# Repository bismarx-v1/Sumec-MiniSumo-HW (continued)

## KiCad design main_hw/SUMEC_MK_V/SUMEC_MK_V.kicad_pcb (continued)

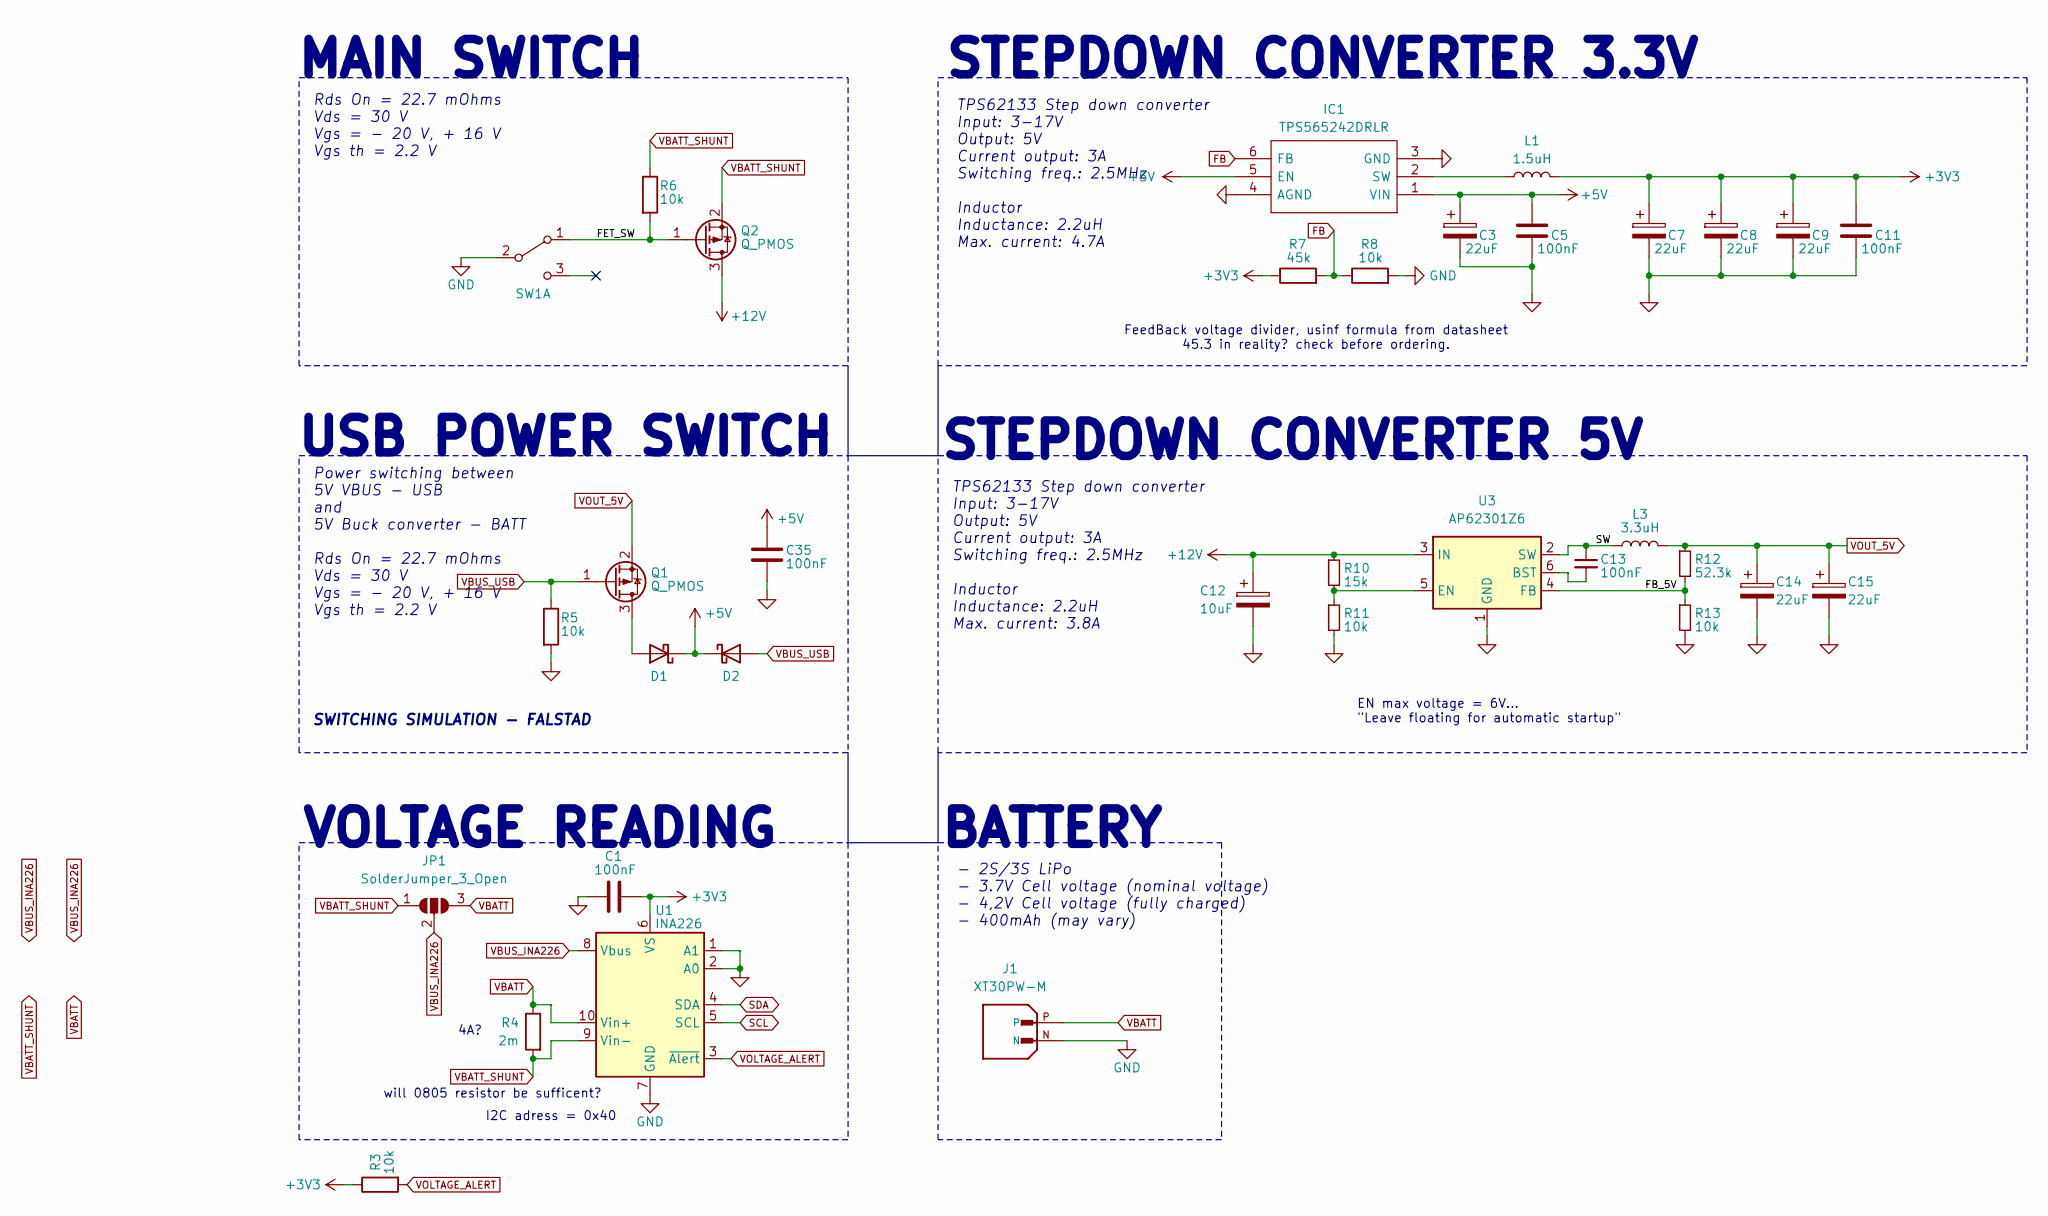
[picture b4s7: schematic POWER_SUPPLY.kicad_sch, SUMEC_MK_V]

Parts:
C1, C13, C35: 100nF; C_0805_2012Metric_Pad1.18x1.45mm_HandSolder
C3, C7, C8, C9, C14, C15: 22uF; CP_EIA-2012-12_Kemet-R_Pad1.30x1.05mm_HandSolder
C5, C11: 100nF; C_0805_2012Metric_Pad1.18x1.45mm_HandSolder; LCSC C49678
C12: 10uF; CP_EIA-3216-18_Kemet-A_Pad1.58x1.35mm_HandSolder
D1, D2: D_Schottky; D_1206_3216Metric_Pad1.42x1.75mm_HandSolder
IC1: TPS565242DRLR; SOT-563; Manufacturer_Part_Number TPS565242DRLR; Mouser Part Number 595-TPS565242DRLR
J1: XT30PW-M; PARTREV 1.2
JP1: SolderJumper_3_Open; SolderJumper-3_P2.0mm_Open_TrianglePad1.0x1.5mm
L1: 1.5uH; L_Vishay_IHLP-1212
L3: 3.3uH; L_Vishay_IHLP-1616
Q1, Q2: Q_PMOS; SOT-23-3
R3, R5, R6, R11, R13: 10k; R_0805_2012Metric_Pad1.20x1.40mm_HandSolder
R4: 2m; R_0805_2012Metric_Pad1.20x1.40mm_HandSolder
R7: 45k; R_0805_2012Metric_Pad1.20x1.40mm_HandSolder; LCSC C17470
R8: 10k; R_0805_2012Metric_Pad1.20x1.40mm_HandSolder; LCSC C17633
R10: 15k; R_0805_2012Metric_Pad1.20x1.40mm_HandSolder
R12: 52.3k; R_0805_2012Metric_Pad1.20x1.40mm_HandSolder
SW1: SW_DPDT_x2; Custom_SPDT_2.5_Switch
U1: INA226; VSSOP-10_3x3mm_P0.5mm
U3: AP62301Z6; SOT-563

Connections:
+3V3: C1.2, C7.1, C8.1, C9.1, C11.1, L1.2, R3.1, R7.1, U1.6 (VS); also elsewhere on the board
+5V: C3.1, C5.1, C35.1, D1.1 (K), D2.1 (K), IC1.1 (VIN), IC1.5 (EN); also elsewhere on the board
+12V: C12.1, Q2.3 (D), R10.1, U3.3 (IN); also elsewhere on the board
/POWER/FB_5V: R12.2, R13.1, U3.4 (FB)
/POWER/FET_SW: Q2.1 (G), R6.2, SW1.1 (A)
/POWER/SW: C13.1, L3.1, U3.2 (SW)
FB: IC1.6 (FB), R7.2, R8.1
GND: C1.1, C3.2, C5.2, C7.2, C8.2, C9.2, C11.2, C12.2, C14.2, C15.2, C35.2, IC1.3 (GND), IC1.4 (AGND), J1.N, R5.2, R8.2, R11.2, R13.2, SW1.2 (B), U1.1 (A1), U1.2 (A0), U1.7 (GND), U3.1 (GND); also elsewhere on the board
unnamed: D1.2 (A), Q1.3 (D)
unnamed: IC1.2 (SW), L1.1
unnamed: C13.2, U3.6 (BST)
unnamed: R10.2, R11.1, U3.5 (EN)
SCL: U1.5 (SCL); also elsewhere on the board
SDA: U1.4 (SDA); also elsewhere on the board
VBATT: J1.P, JP1.3 (B), R4.1, U1.10 (Vin+)
VBATT_SHUNT: JP1.1 (A), Q2.2 (S), R4.2, R6.1, U1.9 (Vin-)
VBUS_INA226: JP1.2 (C), U1.8 (Vbus)
VBUS_USB: D2.2 (A), Q1.1 (G), R5.1; also elsewhere on the board
VOLTAGE_ALERT: R3.2, U1.3 (~Alert); also elsewhere on the board
VOUT_5V: C14.1, C15.1, L3.2, Q1.2 (S), R12.1

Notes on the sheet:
SWITCHING SIMULATION - FALSTAD
TPS62133 Step down converter Input: 3-17V Output: 5V Current output: 3A Switching freq.: 2.5MHz Inductor Inductance: 2.2uH Max. current: 4.7A
BATTERY
USB POWER SWITCH
Power switching between 5V VBUS - USB and 5V Buck converter - BATT
MAIN SWITCH
I2C adress = 0x40
STEPDOWN CONVERTER 3.3V
STEPDOWN CONVERTER 5V
VOLTAGE READING
Rds On = 22.7 mOhms Vds = 30 V Vgs = - 20 V, + 16 V Vgs th = 2.2 V
- 2S/3S LiPo - 3.7V Cell voltage (nominal voltage) - 4,2V Cell voltage (fully charged) - 400mAh (may vary)
TPS62133 Step down converter Input: 3-17V Output: 5V Current output: 3A Switching freq.: 2.5MHz Inductor Inductance: 2.2uH Max. current: 3.8A
4A?
FeedBack voltage divider, usinf formula from datasheet 45.3 in reality? check before ordering.
will 0805 resistor be sufficent?
EN max voltage = 6V... "Leave floating for automatic startup"

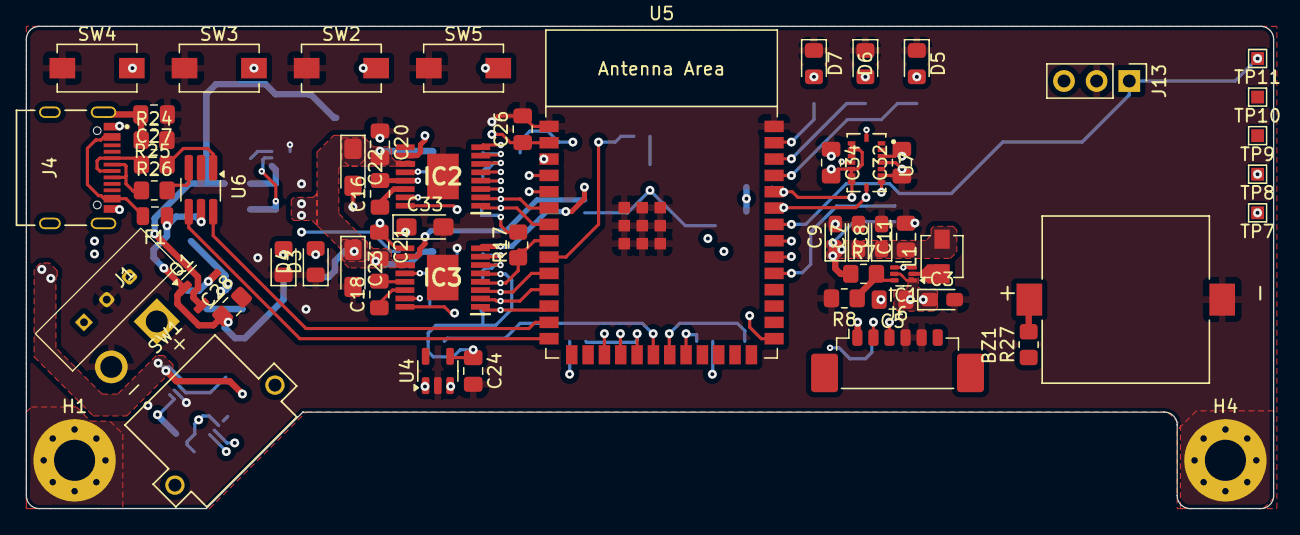
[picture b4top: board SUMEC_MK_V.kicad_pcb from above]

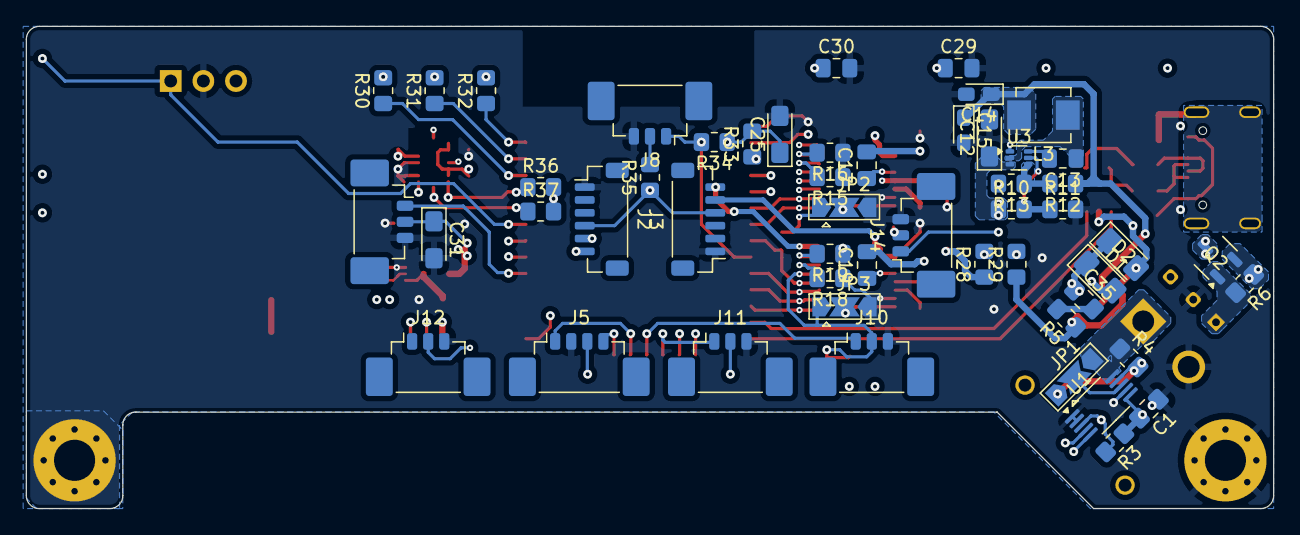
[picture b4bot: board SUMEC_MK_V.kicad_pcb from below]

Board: 4 copper layers, 97.0 x 37.5 mm, 110 parts (52 on the bottom side), 74 nets.

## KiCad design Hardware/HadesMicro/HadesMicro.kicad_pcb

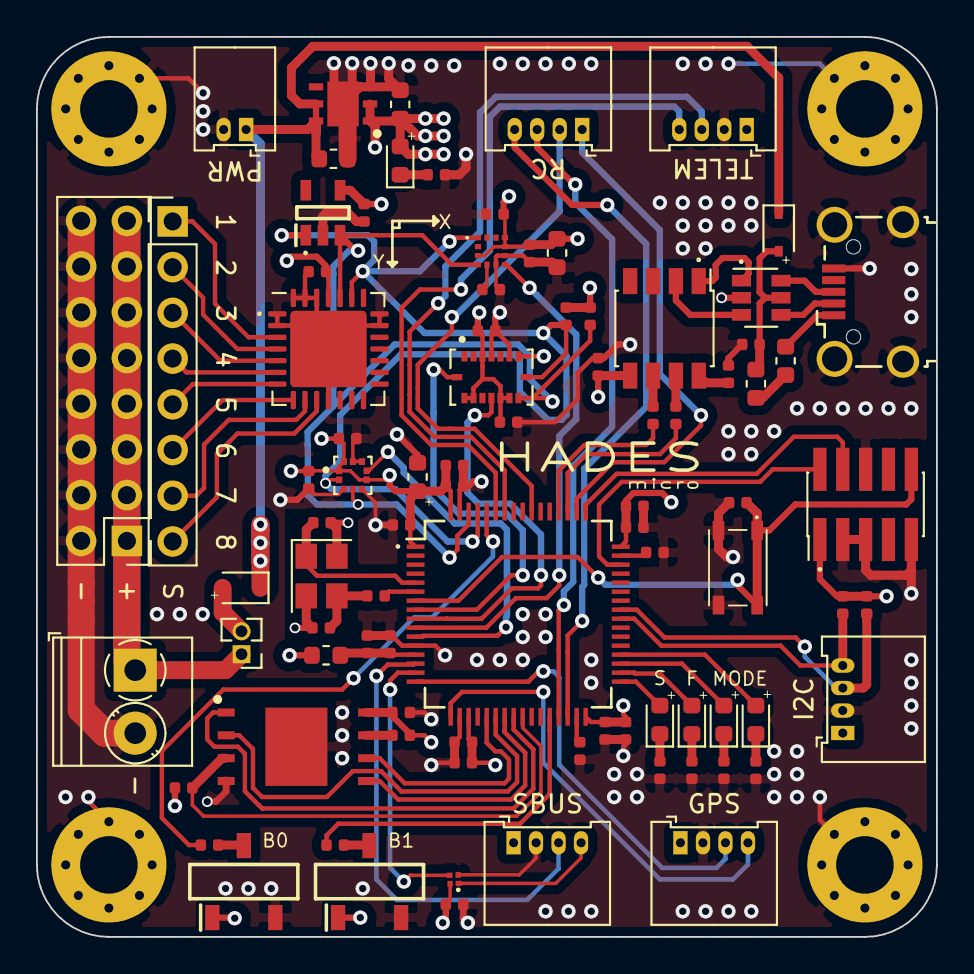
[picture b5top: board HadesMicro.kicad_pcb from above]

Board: 4 copper layers, 50.0 x 50.0 mm, 6 parts (0 on the bottom side), 2 nets.

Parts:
GPS: Conn_01x04; Molex_PicoBlade_53048-0810_1x04_P1.25mm_Horizontal
I2C: Conn_01x04; Molex_PicoBlade_53048-0810_1x04_P1.25mm_Horizontal
PWR: Conn_01x02; Molex_PicoBlade_53048-0410_1x02_P1.25mm_Horizontal
SBUS: Conn_01x04; Molex_PicoBlade_53048-0810_1x04_P1.25mm_Horizontal
SWD: Conn_02x05_Counter_Clockwise; PinHeader_2x05_P1.27mm_Vertical_SMD
TELEM: Conn_01x04; Molex_PicoBlade_53048-0810_1x04_P1.25mm_Horizontal

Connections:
+3V3: GPS.1, I2C.1, SBUS.1, SWD.1, TELEM.1
GND: GPS.2, I2C.2, PWR.2, SBUS.2, SWD.3, SWD.5, SWD.6, SWD.9, TELEM.2

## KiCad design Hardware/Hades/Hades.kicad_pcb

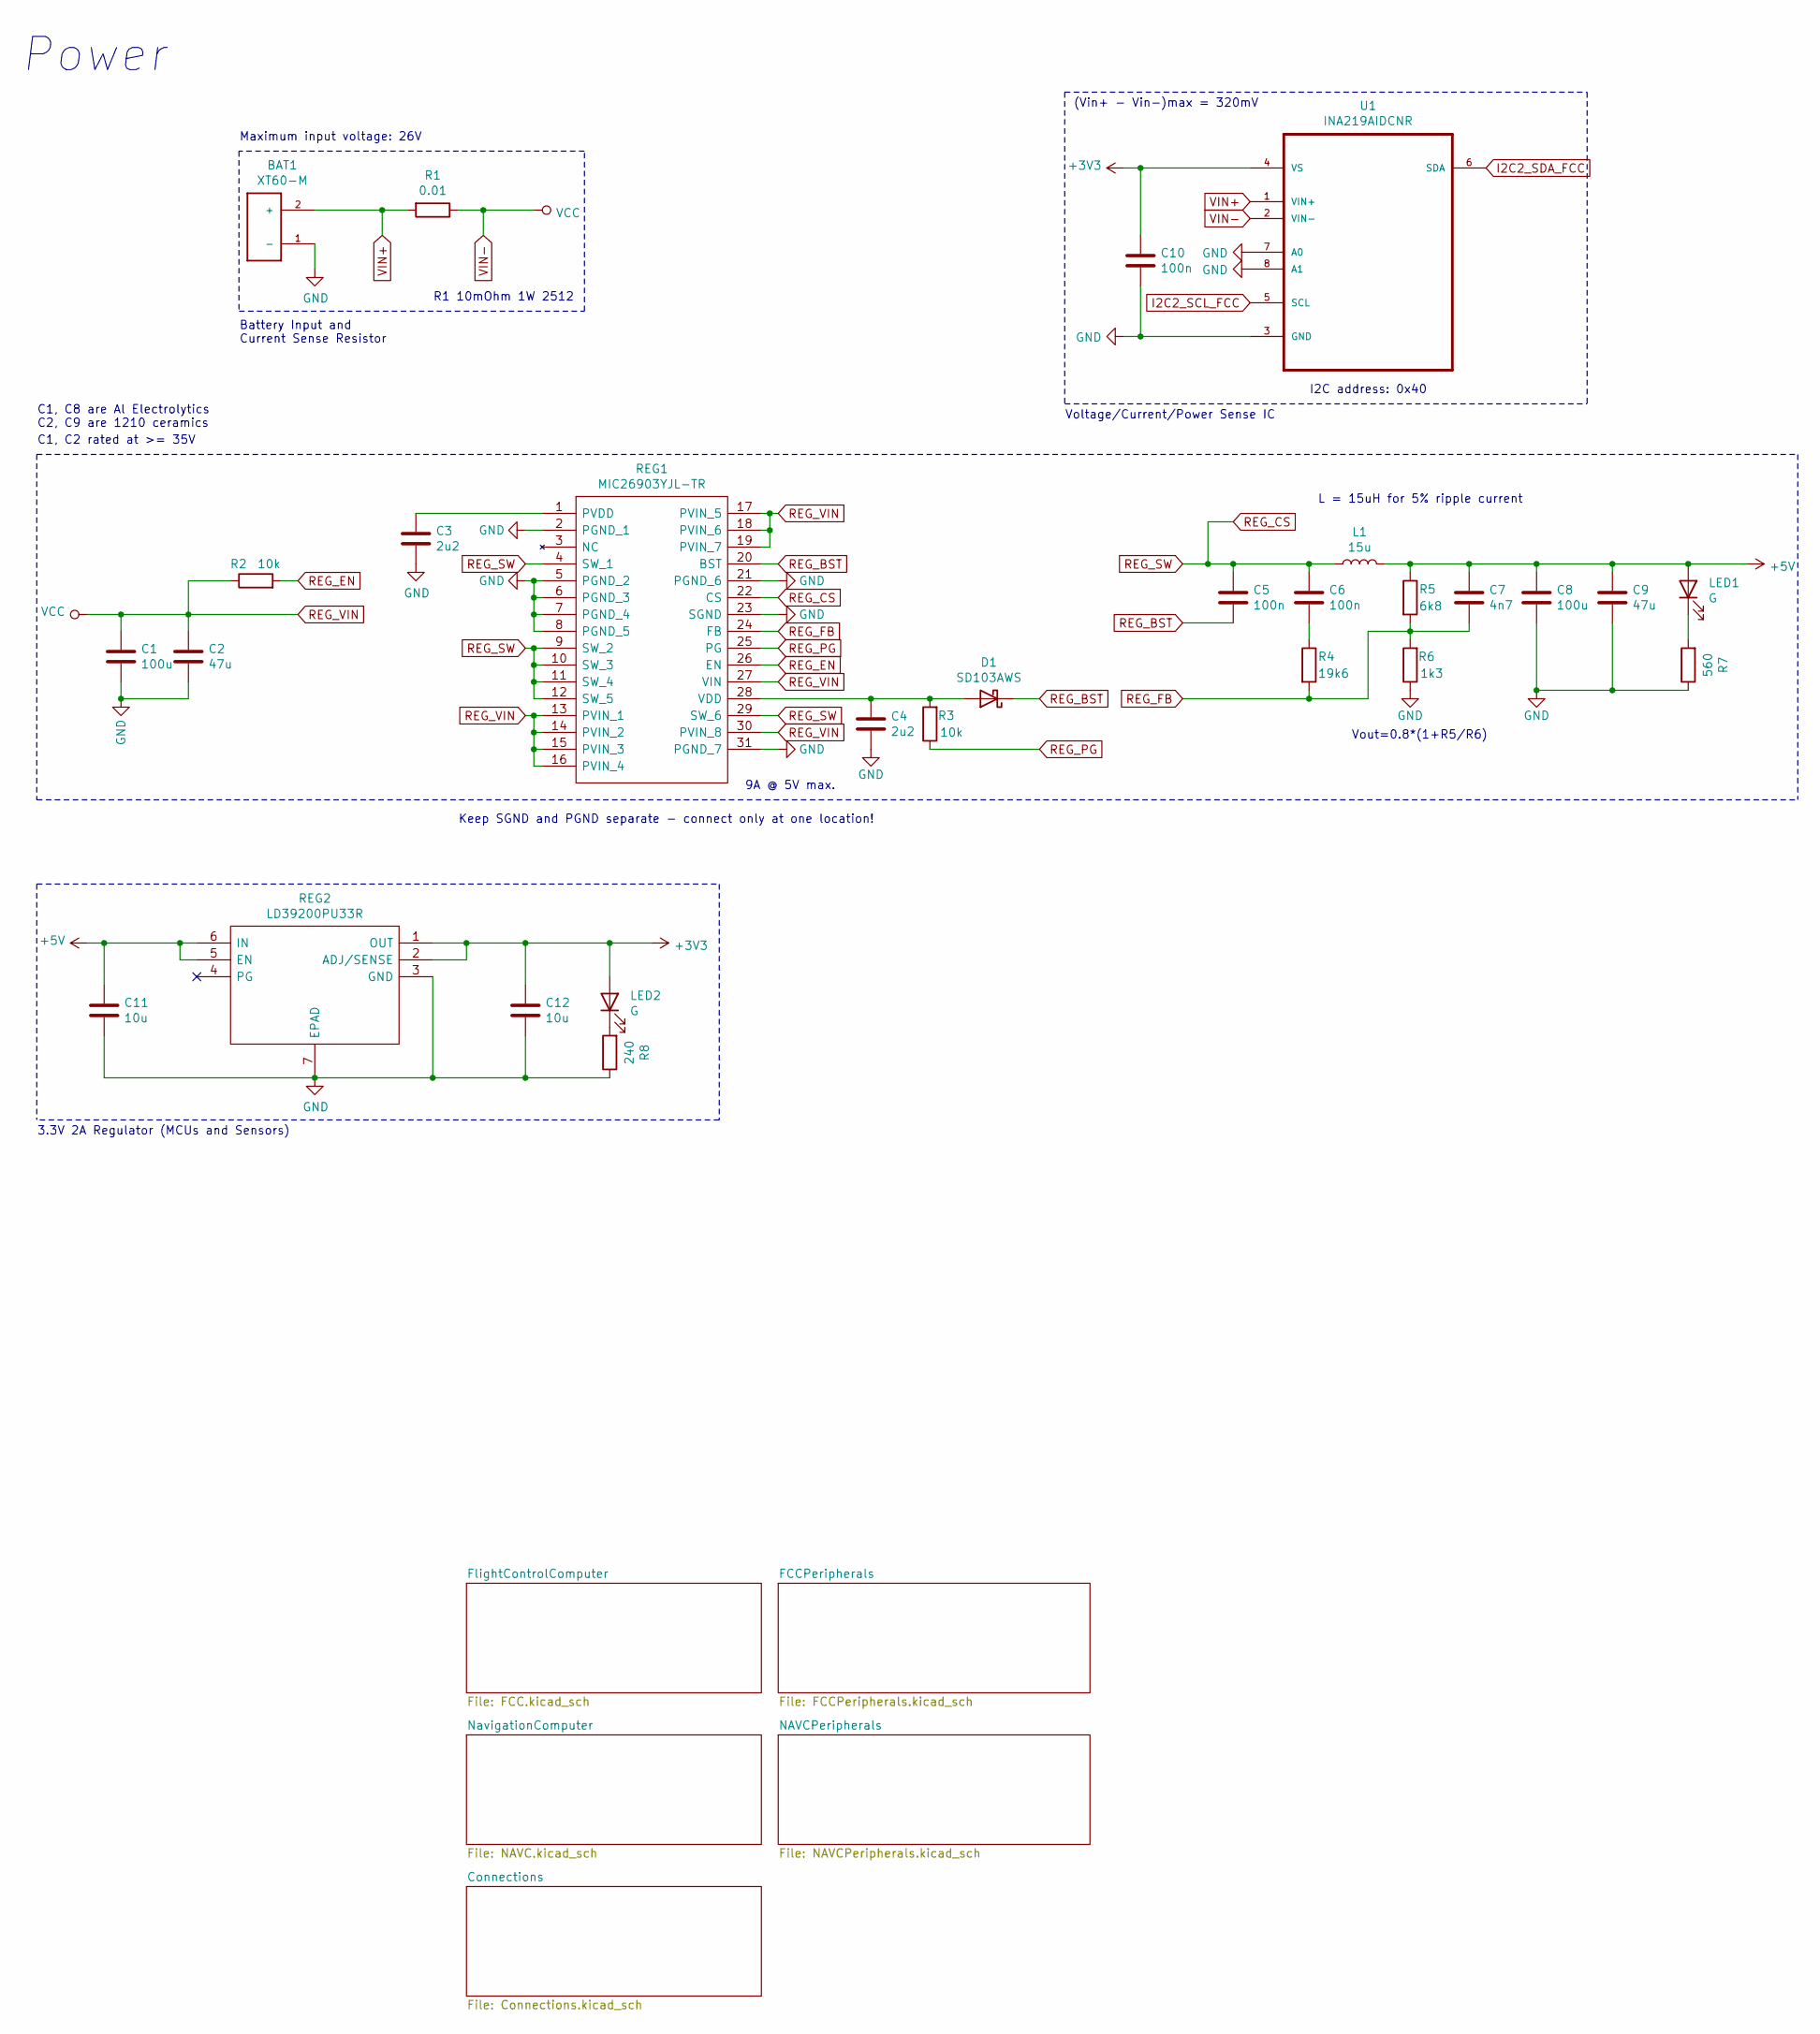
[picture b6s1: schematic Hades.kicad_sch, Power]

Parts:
BAT1: XT60-M; AMASS_XT60-M
C1, C8: 100u; C_Elec_6.3x7.7
C2, C9: 47u; C_1210_3225Metric
C3, C4: 2u2; C_0805_2012Metric
C5, C6: 100n; C_0805_2012Metric
C7: 4n7; C_0805_2012Metric
C10: 100n; C_0402_1005Metric
C11, C12: 10u; C_0603_1608Metric
D1: SD103AWS; D_SOD-323
L1: 15u; INDPM135125X650N
LED1, LED2: G; LED_0603_1608Metric
R1: 0.01; R_2512_6332Metric
R2, R3: 10k; R_0805_2012Metric
R4: 19k6; R_0805_2012Metric
R5: 6k8; R_0805_2012Metric
R6: 1k3; R_0805_2012Metric
R7: 560; R_0603_1608Metric
R8: 240; R_0603_1608Metric
REG1: MIC26903YJL-TR; MIC24054YJLTR; Manufacturer_Part_Number MIC26903YJL-TR; Mouser Part Number 998-MIC26903YJLTR
REG2: LD39200PU33R; SON95P300X300X100-7N-D; Manufacturer_Part_Number LD39200PU33R; Mouser Part Number 511-LD39200PU33R
U1: INA219AIDCNR; SOT65P280X145-8N

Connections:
+3V3: C10.1, C12.1, LED2.2 (A), REG2.1 (OUT), REG2.2 (ADJ/SENSE), U1.4 (VS); also elsewhere on the board
+5V: C7.1, C8.1, C9.1, C11.1, L1.2, LED1.2 (A), R5.1, REG2.5 (EN), REG2.6 (IN); also elsewhere on the board
GND: BAT1.1 (-), C1.2, C2.2, C3.2, C4.2, C8.2, C9.2, C10.2, C11.2, C12.2, R6.1, R7.1, R8.1, REG1.2 (PGND_1), REG1.5 (PGND_2), REG1.6 (PGND_3), REG1.7 (PGND_4), REG1.8 (PGND_5), REG1.21 (PGND_6), REG1.23 (SGND), REG1.31 (PGND_7), REG2.3 (GND), REG2.7 (EPAD), U1.3 (GND), U1.7 (A0), U1.8 (A1); also elsewhere on the board
I2C2_SCL_FCC: U1.5 (SCL); also elsewhere on the board
I2C2_SDA_FCC: U1.6 (SDA); also elsewhere on the board
unnamed: C3.1, REG1.1 (PVDD)
unnamed: C4.1, D1.2 (A), R3.2, REG1.28 (VDD)
unnamed: C6.2, R4.1
unnamed: LED1.1 (K), R7.2
unnamed: LED2.1 (K), R8.2
REG_BST: C5.2, D1.1 (K), REG1.20 (BST)
REG_CS: C5.1, C6.1, L1.1, REG1.4 (SW_1), REG1.9 (SW_2), REG1.10 (SW_3), REG1.11 (SW_4), REG1.12 (SW_5), REG1.22 (CS), REG1.29 (SW_6)
REG_EN: R2.2, REG1.26 (EN)
REG_FB: C7.2, R4.2, R5.2, R6.2, REG1.24 (FB)
REG_PG: R3.1, REG1.25 (PG)
REG_VIN: C1.1, C2.1, R1.1, R2.1, REG1.13 (PVIN_1), REG1.14 (PVIN_2), REG1.15 (PVIN_3), REG1.16 (PVIN_4), REG1.17 (PVIN_5), REG1.18 (PVIN_6), REG1.19 (PVIN_7), REG1.27 (VIN), REG1.30 (PVIN_8), U1.2 (VIN-)
VIN+: BAT1.2 (+), R1.2, U1.1 (VIN+)

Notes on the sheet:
R1 10mOhm 1W 2512
Maximum input voltage: 26V
Power
Battery Input and Current Sense Resistor
(Vin+ - Vin-)max = 320mV
Vout=0.8*(1+R5/R6)
C1, C2 rated at >= 35V
Keep SGND and PGND separate - connect only at one location!
L = 15uH for 5% ripple current
Voltage/Current/Power Sense IC
I2C address: 0x40
9A @ 5V max.
3.3V 2A Regulator (MCUs and Sensors)
C1, C8 are Al Electrolytics C2, C9 are 1210 ceramics

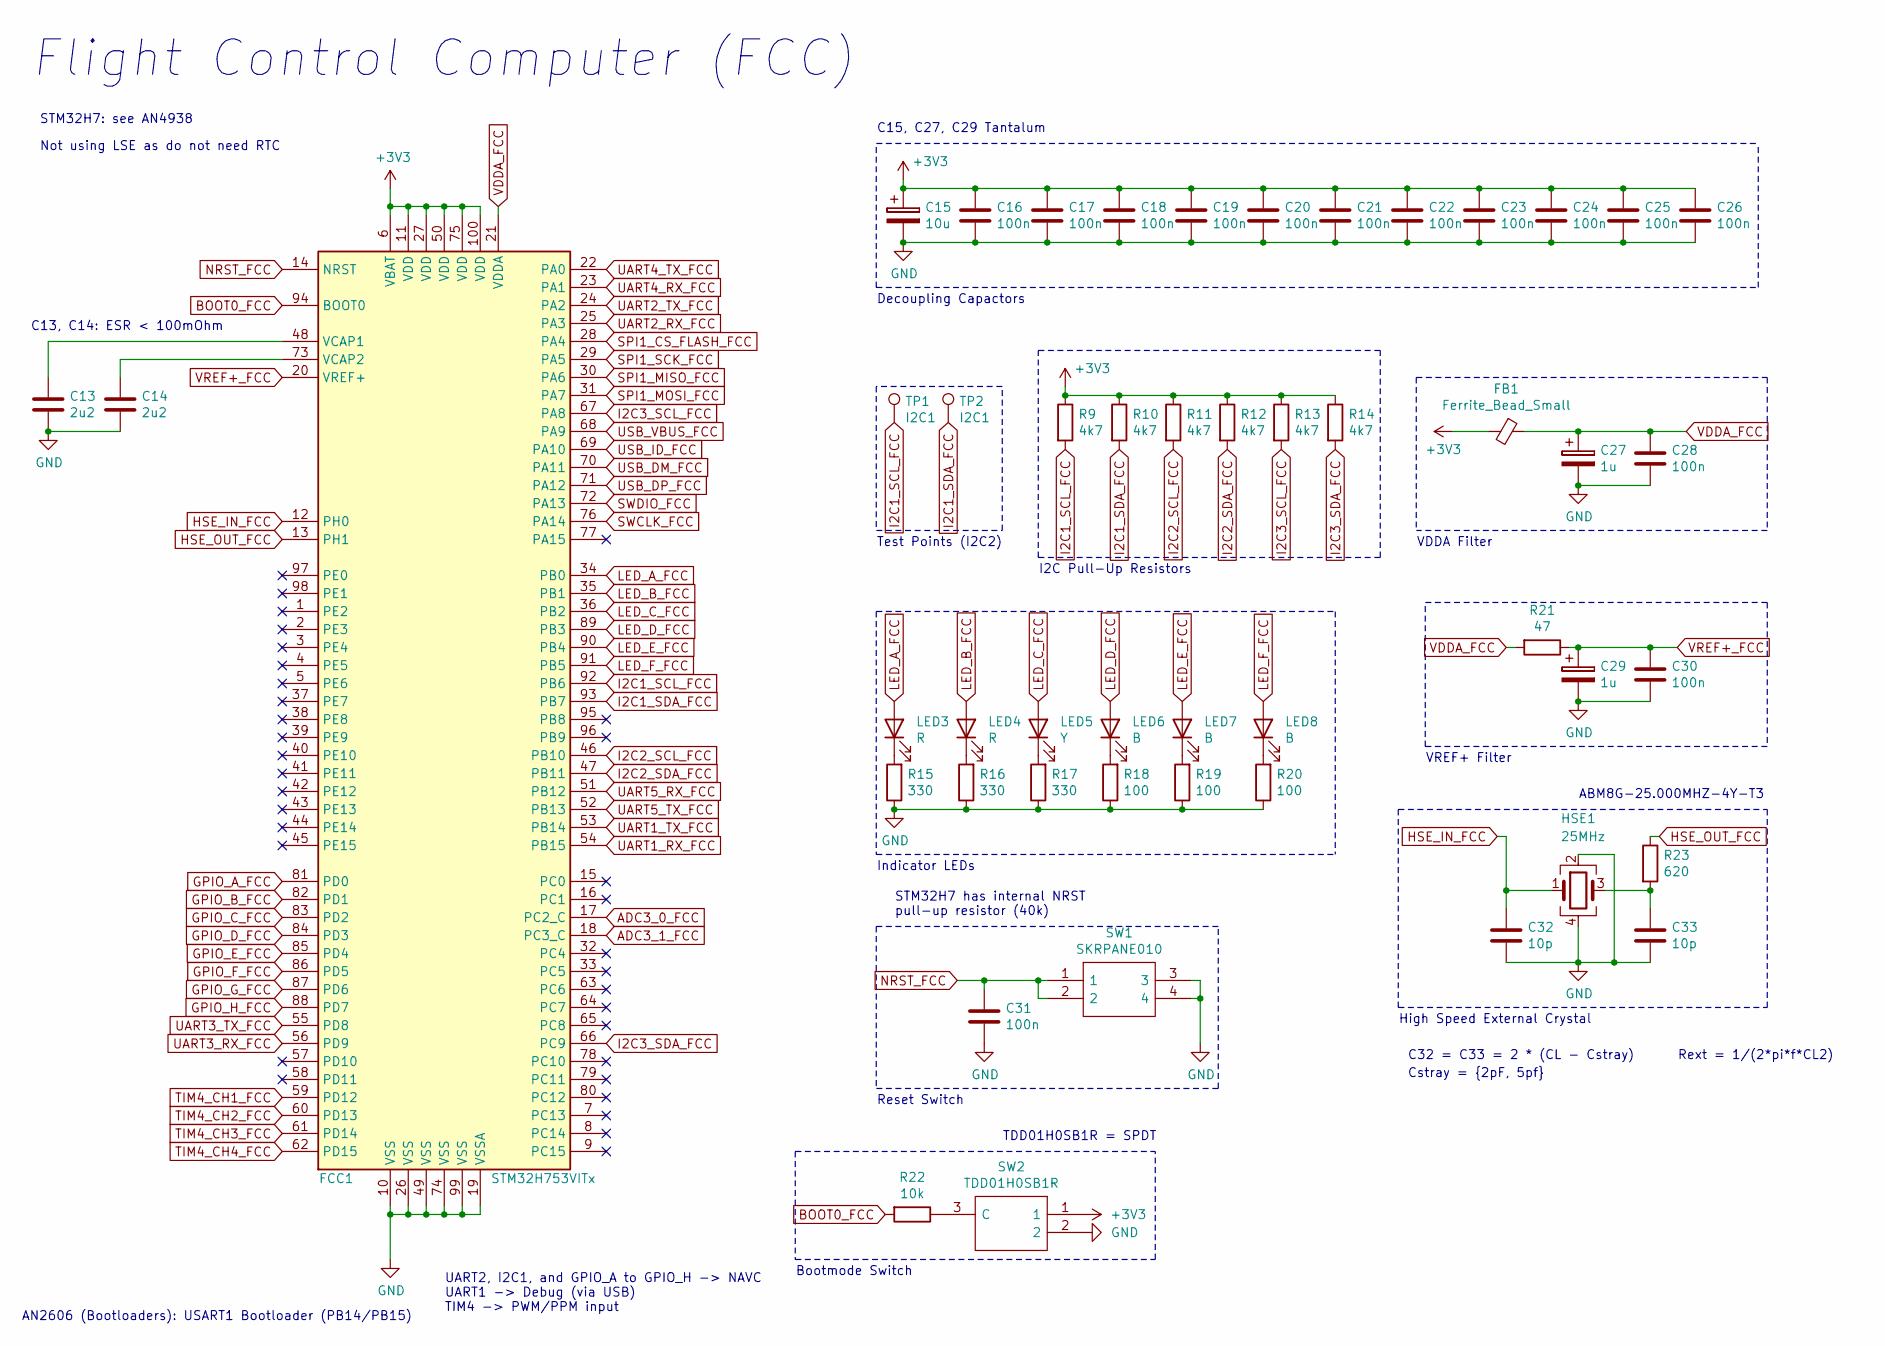
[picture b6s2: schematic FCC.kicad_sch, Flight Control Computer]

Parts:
C13, C14: 2u2; C_0603_1608Metric
C15: 10u; C_0603_1608Metric
C16, C17, C18, C19, C20, C21, C22, C23, C24, C25, C26, C28, C30, C31: 100n; C_0402_1005Metric
C27, C29: 1u; C_0603_1608Metric
C32, C33: 10p; C_0402_1005Metric
FB1: Ferrite_Bead_Small; L_0402_1005Metric
FCC1: STM32H753VITx; LQFP-100_14x14mm_P0.5mm
HSE1: 25MHz; Crystal_SMD_Abracon_ABM8G-4Pin_3.2x2.5mm
LED3, LED4: R; LED_0603_1608Metric
LED5: Y; LED_0603_1608Metric
LED6, LED7, LED8: B; LED_0603_1608Metric
R9, R10, R11, R12, R13, R14: 4k7; R_0402_1005Metric
R15, R16, R17: 330; R_0603_1608Metric
R18, R19, R20: 100; R_0603_1608Metric
R21: 47; R_0402_1005Metric
R22: 10k; R_0402_1005Metric
R23: 620; R_0603_1608Metric
SW1: SKRPANE010; SKRPADE010; Manufacturer_Part_Number SKRPANE010; Mouser Part Number 688-SKRPANE010
SW2: TDD01H0SB1R; SOT175P420X230-3N; Manufacturer_Part_Number TDD01H0SB1R; Mouser Part Number 611-TDD01H0SB1R
TP1, TP2: I2C1; TestPoint_Pad_D1.5mm

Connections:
+3V3: C15.1, C16.1, C17.1, C18.1, C19.1, C20.1, C21.1, C22.1, C23.1, C24.1, C25.1, C26.1, FB1.2, FCC1.6 (VBAT), FCC1.11 (VDD), FCC1.27 (VDD), FCC1.50 (VDD), FCC1.75 (VDD), FCC1.100 (VDD), R9.1, R10.1, R11.1, R12.1, R13.1, R14.1, SW2.1; also elsewhere on the board
BOOT0_FCC: FCC1.94 (BOOT0), R22.2; also elsewhere on the board
GND: C13.2, C14.2, C15.2, C16.2, C17.2, C18.2, C19.2, C20.2, C21.2, C22.2, C23.2, C24.2, C25.2, C26.2, C27.2, C28.2, C29.2, C30.2, C31.2, C32.2, C33.2, FCC1.10 (VSS), FCC1.19 (VSSA), FCC1.26 (VSS), FCC1.49 (VSS), FCC1.74 (VSS), FCC1.99 (VSS), HSE1.2, HSE1.4, R15.1, R16.1, R17.1, R18.1, R19.1, R20.1, SW1.3, SW1.4, SW2.2; also elsewhere on the board
HSE_IN_FCC: C32.1, FCC1.12 (PH0), HSE1.1; also elsewhere on the board
HSE_OUT_FCC: FCC1.13 (PH1), R23.1; also elsewhere on the board
I2C1_SCL_FCC: FCC1.92 (PB6), R9.2, TP1.1; also elsewhere on the board
I2C1_SDA_FCC: FCC1.93 (PB7), R10.2, TP2.1; also elsewhere on the board
I2C2_SCL_FCC: FCC1.46 (PB10), R11.2; also elsewhere on the board
I2C2_SDA_FCC: FCC1.47 (PB11), R12.2; also elsewhere on the board
I2C3_SCL_FCC: FCC1.67 (PA8), R13.2; also elsewhere on the board
I2C3_SDA_FCC: FCC1.66 (PC9), R14.2; also elsewhere on the board
LED_A_FCC: FCC1.34 (PB0), LED3.2 (A); also elsewhere on the board
LED_B_FCC: FCC1.35 (PB1), LED4.2 (A); also elsewhere on the board
LED_C_FCC: FCC1.36 (PB2), LED5.2 (A); also elsewhere on the board
LED_D_FCC: FCC1.89 (PB3), LED6.2 (A); also elsewhere on the board
LED_E_FCC: FCC1.90 (PB4), LED7.2 (A); also elsewhere on the board
LED_F_FCC: FCC1.91 (PB5), LED8.2 (A); also elsewhere on the board
NRST_FCC: C31.1, FCC1.14 (NRST), SW1.1, SW1.2; also elsewhere on the board
unnamed 65: C13.1, FCC1.48 (VCAP1); also elsewhere on the board
unnamed 66: C14.1, FCC1.73 (VCAP2); also elsewhere on the board
unnamed: C33.1, HSE1.3, R23.2
unnamed: LED3.1 (K), R15.2
unnamed: LED4.1 (K), R16.2
unnamed: LED5.1 (K), R17.2
unnamed: LED6.1 (K), R18.2
unnamed: LED7.1 (K), R19.2
unnamed: LED8.1 (K), R20.2
unnamed: R22.1, SW2.3 (C)
VDDA_FCC: C27.1, C28.1, FB1.1, FCC1.21 (VDDA), R21.2; also elsewhere on the board
VREF+_FCC: C29.1, C30.1, FCC1.20 (VREF+), R21.1; also elsewhere on the board

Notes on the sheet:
Rext = 1/(2*pi*f*CL2)
Indicator LEDs
UART2, I2C1, and GPIO_A to GPIO_H -> NAVC UART1 -> Debug (via USB) TIM4 -> PWM/PPM input
VREF+ Filter
STM32H7: see AN4938
Bootmode Switch
I2C Pull-Up Resistors
High Speed External Crystal
Flight Control Computer (FCC)
Reset Switch
C15, C27, C29 Tantalum
C13, C14: ESR < 100mOhm
Not using LSE as do not need RTC
C32 = C33 = 2 * (CL - Cstray)
AN2606 (Bootloaders): USART1 Bootloader (PB14/PB15)
TDD01H0SB1R = SPDT
Cstray = {2pF, 5pf}
STM32H7 has internal NRST pull-up resistor (40k)
Decoupling Capactors
Test Points (I2C2)
VDDA Filter
ABM8G-25.000MHZ-4Y-T3

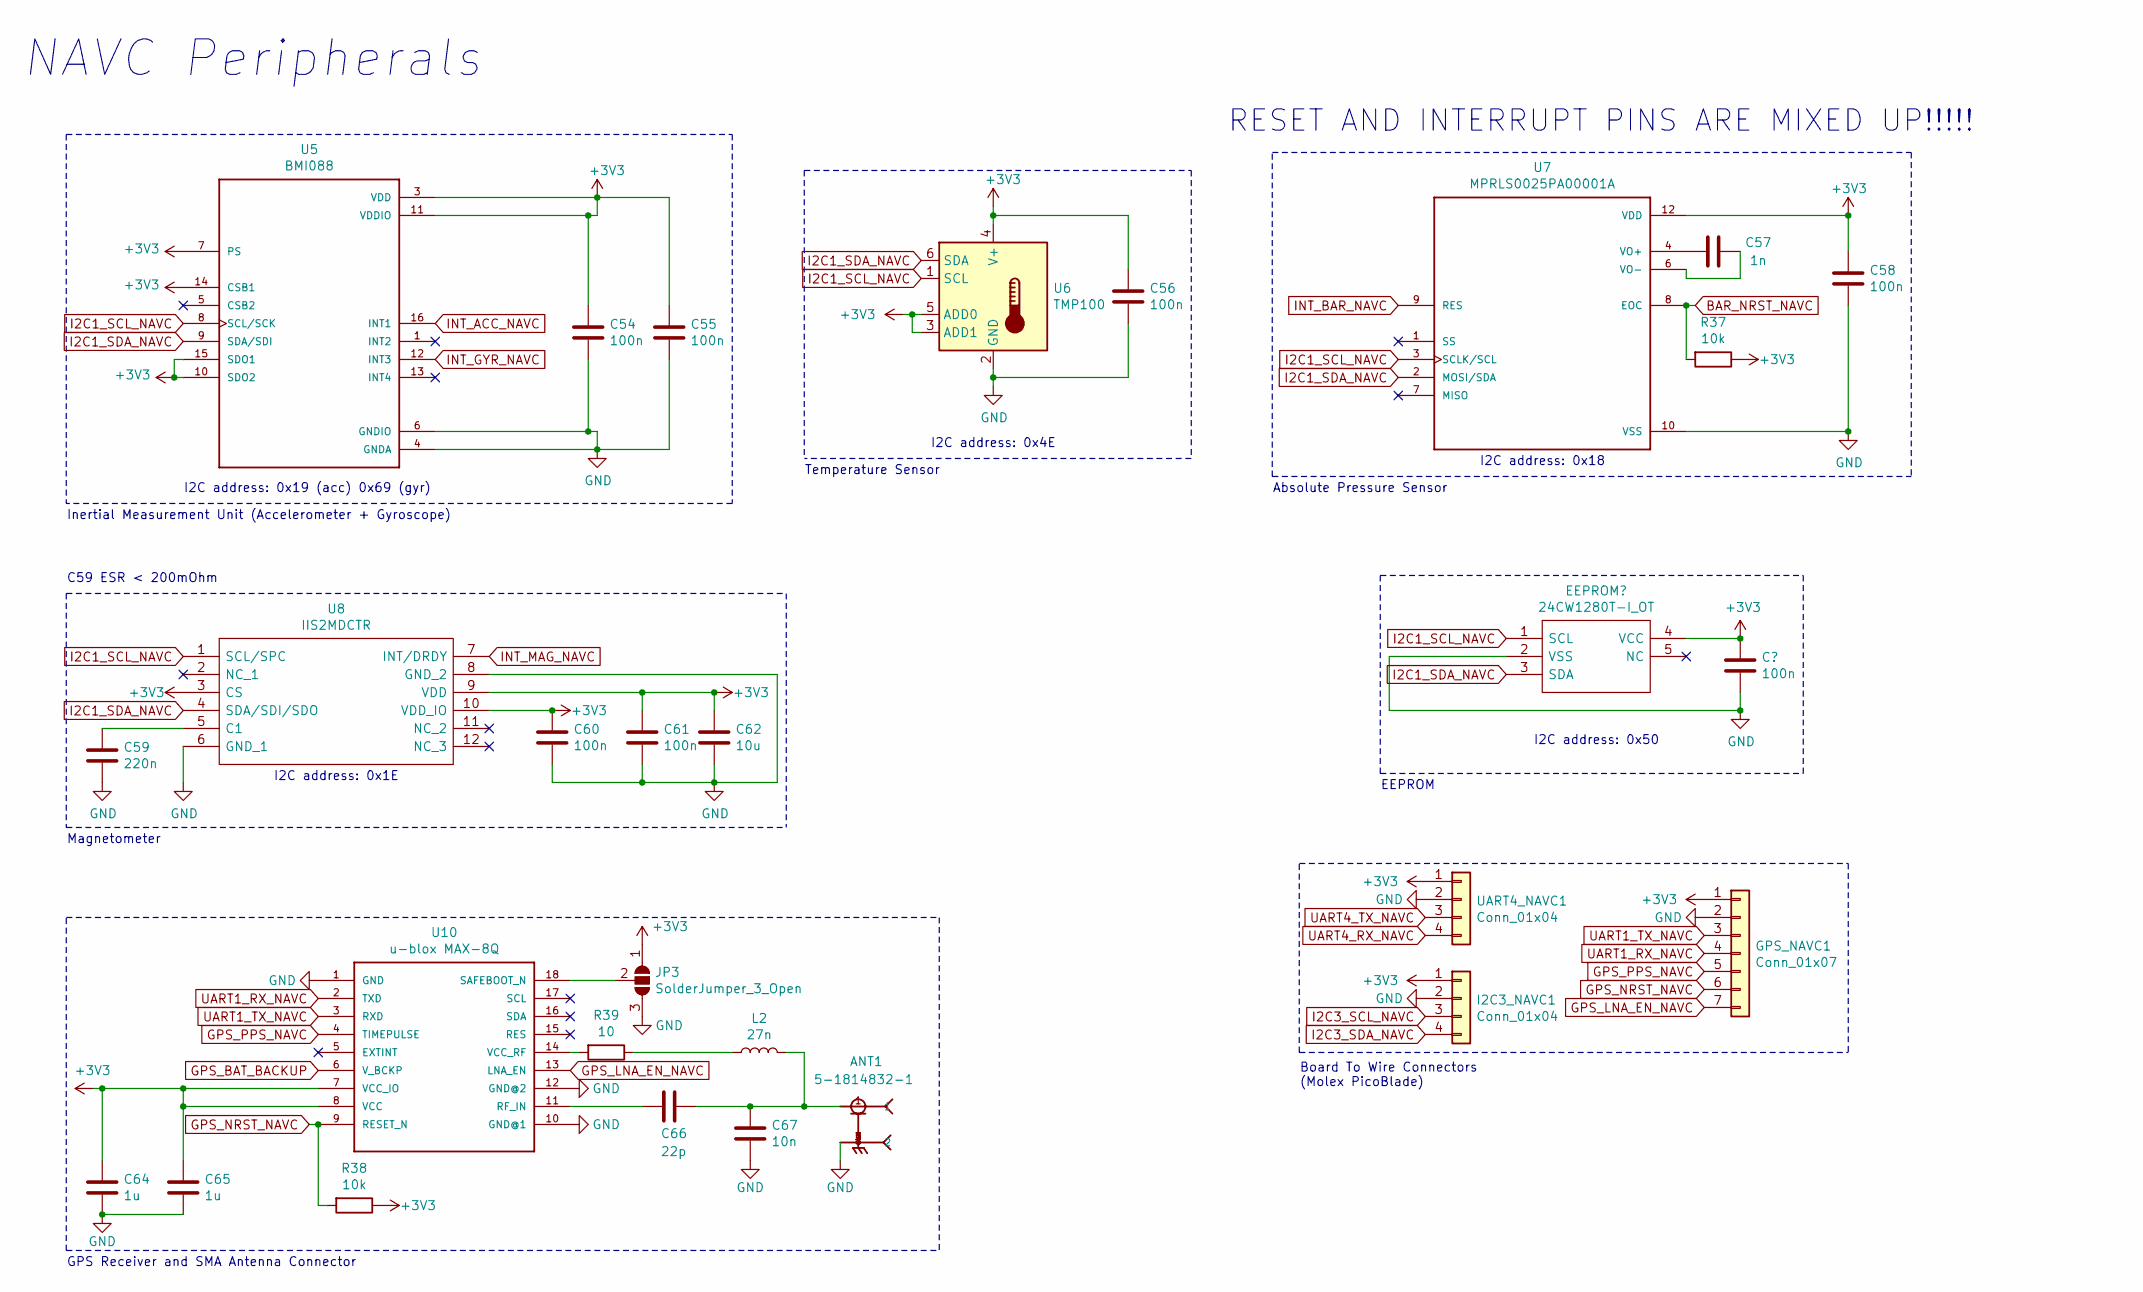
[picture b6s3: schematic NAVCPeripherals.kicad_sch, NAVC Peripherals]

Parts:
ANT1: 5-1814832-1; TE_5-1814832-1
C54, C55, C56, C58, C60, C61, C63: 100n; C_0402_1005Metric
C57: 1n; C_0402_1005Metric
C59: 220n; C_0603_1608Metric
C62: 10u; C_0603_1608Metric
C64, C65: 1u; C_0603_1608Metric
C66: 22p; C_0402_1005Metric
C67: 10n; C_0402_1005Metric
GPS_NAVC1: Conn_01x07; Molex_PicoBlade_53048-0710_1x07_P1.25mm_Horizontal
I2C3_NAVC1: Conn_01x04; Molex_PicoBlade_53048-0410_1x04_P1.25mm_Horizontal
JP3: SolderJumper_3_Open; SolderJumper-3_P1.3mm_Open_RoundedPad1.0x1.5mm
L2: 27n; L_0402_1005Metric
R37, R38: 10k; R_0402_1005Metric
R39: 10; R_0402_1005Metric
U5: BMI088; PQFN50P450X300X100-16N
U6: TMP100; SOT-23-6
U7: MPRLS0025PA00001A; XDCR_MPRLS0025PA00001A
U8: IIS2MDCTR; Manufacturer_Part_Number IIS2MDCTR; Mouser Part Number 511-IIS2MDCTR
U9: 24CW1280T-I_OT; SOT95P280X145-5N; Manufacturer_Part_Number 24CW1280T-I/OT; Mouser Part Number 579-24CW1280T-I/OT
U10: u-blox MAX-8Q; GPS18P-SMD-1.1-10X9.6MM
UART4_NAVC1: Conn_01x04; Molex_PicoBlade_53048-0410_1x04_P1.25mm_Horizontal

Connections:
+3V3: C54.1, C55.1, C56.1, C58.1, C60.1, C61.1, C62.1, C63.1, C64.1, C65.1, GPS_NAVC1.1, I2C3_NAVC1.1, JP3.1 (A), R37.1, R38.1, U5.3 (VDD), U5.7 (PS), U5.10 (SDO2), U5.11 (VDDIO), U5.14 (CSB1), U5.15 (SDO1), U6.3 (ADD1), U6.4 (V+), U6.5 (ADD0), U7.12 (VDD), U8.3 (CS), U8.9 (VDD), U8.10 (VDD_IO), U9.4 (VCC), U10.7 (VCC_IO), U10.8 (VCC), UART4_NAVC1.1; also elsewhere on the board
BAR_NRST_NAVC: R37.2, U7.8 (EOC); also elsewhere on the board
GND: ANT1.2, ANT1.3 (2), ANT1.4 (2), ANT1.5 (2), C54.2, C55.2, C56.2, C58.2, C59.2, C60.2, C61.2, C62.2, C63.2, C64.2, C65.2, C67.2, GPS_NAVC1.2, I2C3_NAVC1.2, JP3.3 (B), U5.4 (GNDA), U5.6 (GNDIO), U6.2 (GND), U7.10 (VSS), U8.6 (GND_1), U8.8 (GND_2), U9.2 (VSS), U10.1 (GND), U10.10 (GND@1), U10.12 (GND@2), UART4_NAVC1.2; also elsewhere on the board
GPS_BAT_BACKUP: U10.6 (V_BCKP); also elsewhere on the board
GPS_LNA_EN_NAVC: GPS_NAVC1.7, U10.13 (LNA_EN); also elsewhere on the board
GPS_NRST_NAVC: GPS_NAVC1.6, R38.2, U10.9 (RESET_N); also elsewhere on the board
GPS_PPS_NAVC: GPS_NAVC1.5, U10.4 (TIMEPULSE); also elsewhere on the board
I2C1_SCL_NAVC: U5.8 (SCL/SCK), U6.1 (SCL), U7.3 (SCLK/SCL), U8.1 (SCL/SPC), U9.1 (SCL); also elsewhere on the board
I2C1_SDA_NAVC: U5.9 (SDA/SDI), U6.6 (SDA), U7.2 (MOSI/SDA), U8.4 (SDA/SDI/SDO), U9.3 (SDA); also elsewhere on the board
INT_ACC_NAVC: U5.16 (INT1); also elsewhere on the board
INT_BAR_NAVC: U7.9 (RES); also elsewhere on the board
INT_GYR_NAVC: U5.12 (INT3); also elsewhere on the board
INT_MAG_NAVC: U8.7 (INT/DRDY); also elsewhere on the board
unnamed: ANT1.1, C66.1, C67.1, L2.2
unnamed: C57.1, U7.6 (VO-)
unnamed: C57.2, U7.4 (VO+)
unnamed: C59.1, U8.5 (C1)
unnamed: C66.2, U10.11 (RF_IN)
unnamed: JP3.2 (C), U10.18 (SAFEBOOT_N)
unnamed: L2.1, R39.1
unnamed: R39.2, U10.14 (VCC_RF)
UART1_RX_NAVC: GPS_NAVC1.4, U10.2 (TXD); also elsewhere on the board
UART1_TX_NAVC: GPS_NAVC1.3, U10.3 (RXD); also elsewhere on the board

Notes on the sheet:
Absolute Pressure Sensor
Board To Wire Connectors (Molex PicoBlade)
EEPROM
I2C address: 0x4E
C59 ESR < 200mOhm
I2C address: 0x50
I2C address: 0x1E
Inertial Measurement Unit (Accelerometer + Gyroscope)
NAVC Peripherals
Magnetometer
GPS Receiver and SMA Antenna Connector
Temperature Sensor
I2C address: 0x19 (acc) 0x69 (gyr)
RESET AND INTERRUPT PINS ARE MIXED UP!!!!!
I2C address: 0x18
